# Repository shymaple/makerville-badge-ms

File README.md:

- `mkdir badge-workspace`
- `cd badge-workspace`
- `west init -m git@github.com:makerville/makerville-badge.git --mr master`
- `west update`
- `west blobs fetch hal_espressif`
- `cd makerville-badge`
- `make`
- `make flash monitor`

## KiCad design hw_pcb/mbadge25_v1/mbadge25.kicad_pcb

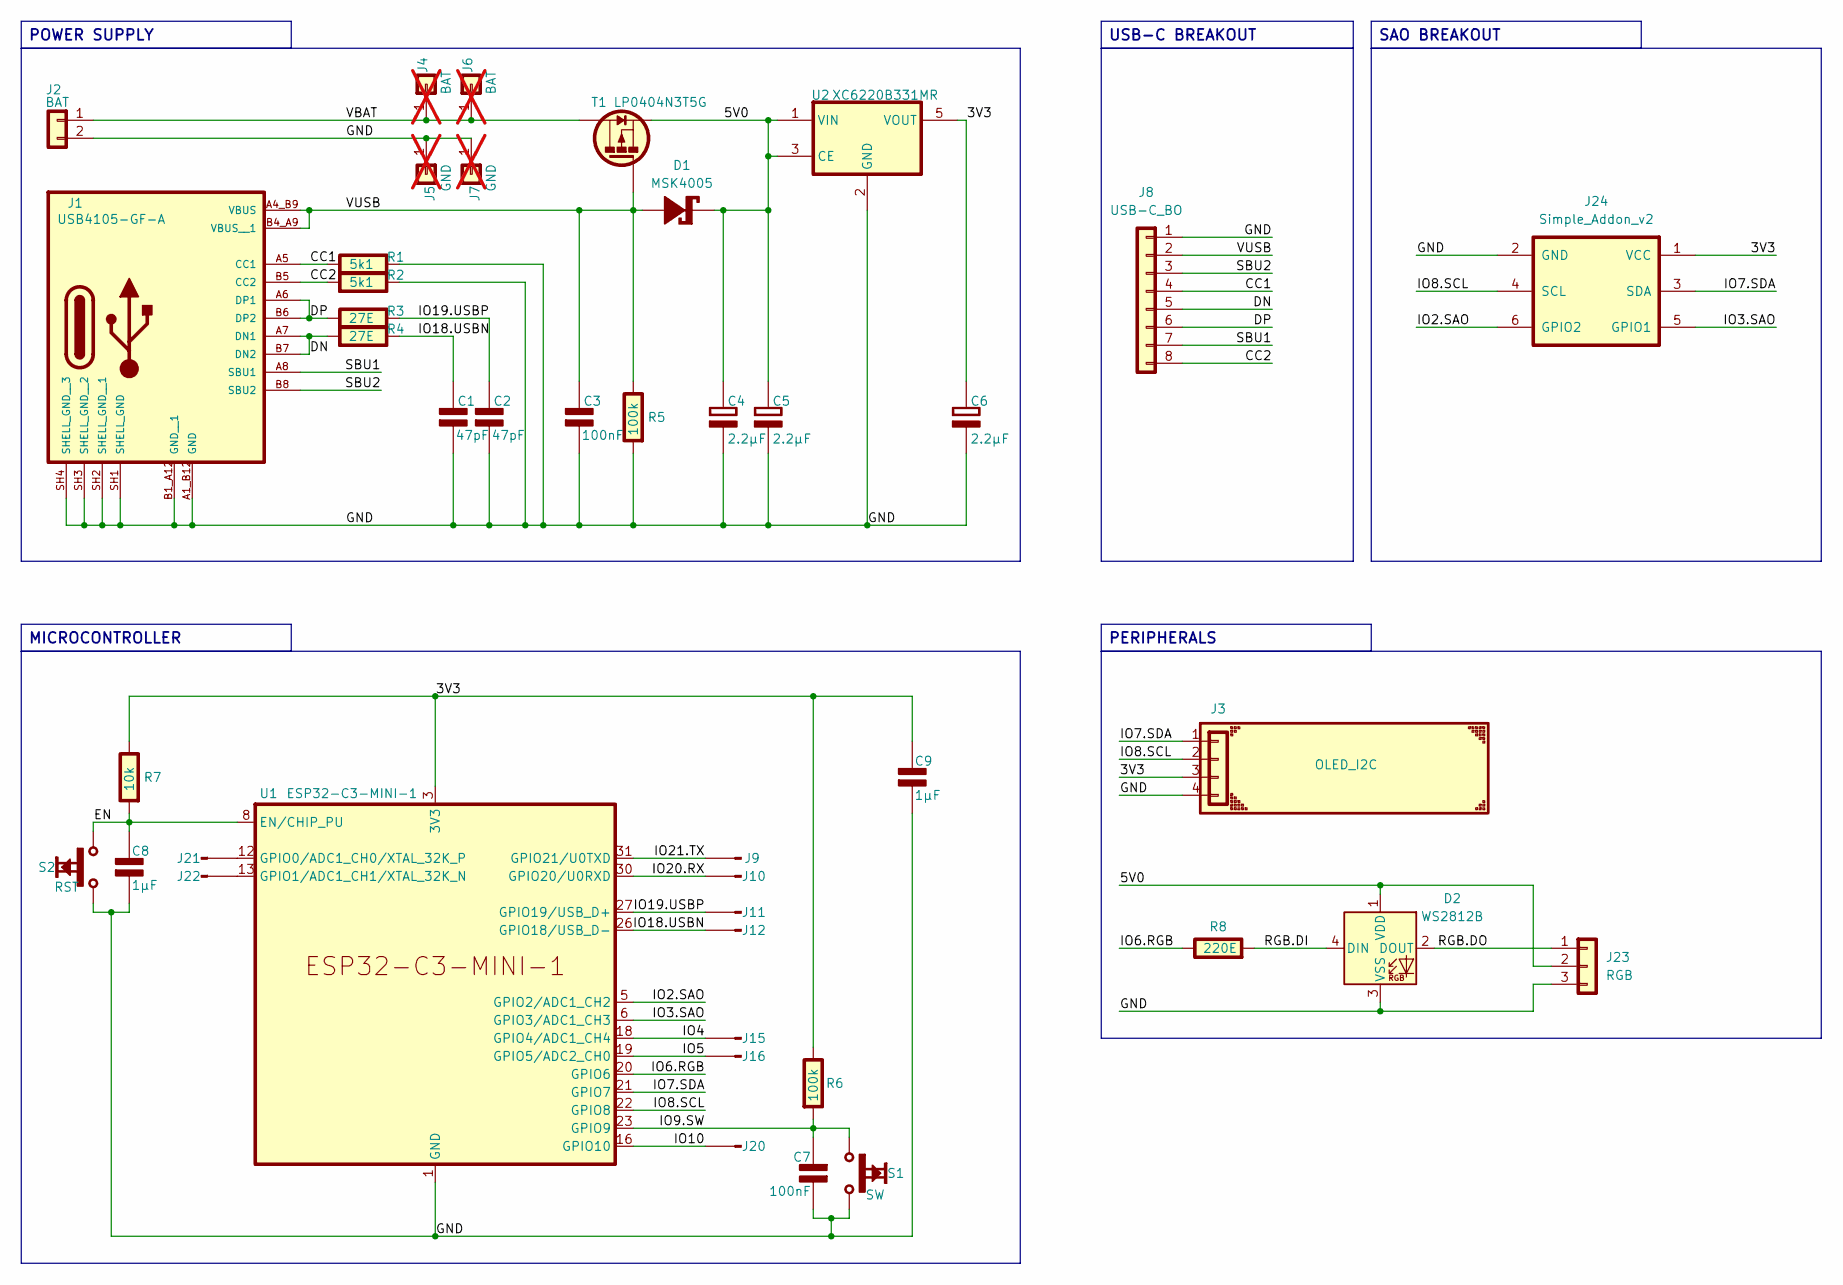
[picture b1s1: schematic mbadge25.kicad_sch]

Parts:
C1, C2: 47pF; C_1206_3216Metric_Pad1.33x1.80mm; Rating V
C3, C7: 100nF; C_1206_3216Metric_Pad1.33x1.80mm; Rating V
C4, C5, C6: 2.2µF; C_1206_3216Metric_Pad1.33x1.80mm; Rating V
C8, C9: 1µF; C_1206_3216Metric_Pad1.33x1.80mm; Rating V
D1: MSK4005; D_SOD-523; Rating V/A
D2: WS2812B; LED_WS2812B_PLCC4_5.0x5.0mm_P3.2mm
J1: USB4105-GF-A; GCT_USB4105-GF-A
J2: BAT; PinHeader_1x02_P2.54mm_Vertical
J3: OLED_I2C; OLED_128x32
J4: BAT; Pad_6.0mm_Drill3.0mm; not fitted
J5: GND; Pad_6.0mm_Drill3.0mm; not fitted
J6: BAT; Pad_1.2mm_Drill0.7mm; not fitted
J7: GND; Pad_1.2mm_Drill0.7mm; not fitted
J8: USB-C_BO; USB_C_BO
J9: Conn_IO21.TX; PinHeader_1x01_P1.27mm_Vertical
J10: Conn_IO20.RX; PinHeader_1x01_P1.27mm_Vertical
J11: Conn_IO19.USBP; PinHeader_1x01_P1.27mm_Vertical
J12: Conn_IO18.USBN; PinHeader_1x01_P1.27mm_Vertical
J15: Conn_IO4; PinHeader_1x01_P1.27mm_Vertical
J16: Conn_IO5; PinHeader_1x01_P1.27mm_Vertical
J20: Conn_IO10; PinHeader_1x01_P1.27mm_Vertical
J21: Conn_IO00; PinHeader_1x01_P1.27mm_Vertical
J22: Conn_IO01; PinHeader_1x01_P1.27mm_Vertical
J23: RGB; PinSocket_1x03_P1.27mm_Vertical
J24: Simple_Addon_v2; Simple_Addon_v2-BADGE-2x3
R1, R2: 5k1; R_1206_3216Metric_Pad1.30x1.75mm; Rating W
R3, R4: 27E; R_1206_3216Metric_Pad1.30x1.75mm; Rating W
R5, R6: 100k; R_1206_3216Metric_Pad1.30x1.75mm; Rating W
R7: 10k; R_1206_3216Metric_Pad1.30x1.75mm; Rating W
R8: 220E; R_1206_3216Metric_Pad1.30x1.75mm; Rating W
S1: SW; SW_SPST; Rating V/A
S2: RST; SW_SPST; Rating V/A
T1: LP0404N3T5G; SOT-23-3
U1: ESP32-C3-MINI-1
U2: XC6220B331MR; SOT-23-5_HandSoldering

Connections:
/3V3: C6.1 (+), C9.1 (+), J3.3, J24.1 (VCC), R6.2 (-), R7.2 (-), U1.3 (3V3), U2.5 (VOUT)
/5V0: C4.1 (+), C5.1 (+), D1.1 (K-), D2.1 (VDD), J23.2, T1.3 (S), U2.1 (VIN), U2.3 (CE)
/CC1: J1.A5 (CC1), J8.4, R1.1 (+)
/CC2: J1.B5 (CC2), J8.8, R2.1 (+)
/DN: J1.A7 (DN1), J1.B7 (DN2), J8.5, R4.1 (+)
/DP: J1.A6 (DP1), J1.B6 (DP2), J8.6, R3.1 (+)
/EN: C8.1 (+), R7.1 (+), S2.1, U1.8 (EN/CHIP_PU)
/GND: C1.2 (-), C2.2 (-), C3.2 (-), C4.2 (-), C5.2 (-), C6.2 (-), C7.2 (-), C8.2 (-), C9.2 (-), D2.3 (VSS), J1.A1_B12 (GND), J1.B1_A12 (GND__1), J1.SH1 (SHELL_GND), J1.SH2 (SHELL_GND__1), J1.SH3 (SHELL_GND__2), J1.SH4 (SHELL_GND__3), J2.2, J3.4, J5.1, J7.1, J8.1, J23.3, J24.2 (GND), R1.2 (-), R2.2 (-), R5.1 (+), S1.2, S2.2, U1.1 (GND), U1.2 (GND), U1.11 (GND), U1.14 (GND), U1.36 (GND), U1.37 (GND), U1.38 (GND), U1.39 (GND), U1.40 (GND), U1.41 (GND), U1.42 (GND), U1.43 (GND), U1.44 (GND), U1.45 (GND), U1.46 (GND), U1.47 (GND), U1.48 (GND), U1.49 (GND), U1.50 (GND), U1.51 (GND), U1.52 (GND), U1.53 (GND), U2.2 (GND)
/IO2.SAO: J24.6 (GPIO2), U1.5 (GPIO2/ADC1_CH2)
/IO3.SAO: J24.5 (GPIO1), U1.6 (GPIO3/ADC1_CH3)
/IO4: J15.1, U1.18 (GPIO4/ADC1_CH4)
/IO5: J16.1, U1.19 (GPIO5/ADC2_CH0)
/IO6.RGB: R8.2 (-), U1.20 (GPIO6)
/IO7.SDA: J3.1, J24.3 (SDA), U1.21 (GPIO7)
/IO8.SCL: J3.2, J24.4 (SCL), U1.22 (GPIO8)
/IO9.SW: C7.1 (+), R6.1 (+), S1.1, U1.23 (GPIO9)
/IO10: J20.1, U1.16 (GPIO10)
/IO18.USBN: C1.1 (+), J12.1, R4.2 (-), U1.26 (GPIO18/USB_D-)
/IO19.USBP: C2.1 (+), J11.1, R3.2 (-), U1.27 (GPIO19/USB_D+)
/IO20.RX: J10.1, U1.30 (GPIO20/U0RXD)
/IO21.TX: J9.1, U1.31 (GPIO21/U0TXD)
/RGB.DI: D2.4 (DIN), R8.1 (+)
/RGB.DO: D2.2 (DOUT), J23.1
/SBU1: J1.A8 (SBU1), J8.7
/SBU2: J1.B8 (SBU2), J8.3
/VBAT: J2.1, J4.1, J6.1, T1.1 (D)
/VUSB: C3.1 (+), D1.2 (A+), J1.A4_B9 (VBUS), J1.B4_A9 (VBUS__1), J8.2, R5.2 (-), T1.2 (G)
unnamed: J21.1, U1.12 (GPIO0/ADC1_CH0/XTAL_32K_P)
unnamed: J22.1, U1.13 (GPIO1/ADC1_CH1/XTAL_32K_N)

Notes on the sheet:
MICROCONTROLLER
POWER SUPPLY
USB-C BREAKOUT
SAO BREAKOUT
PERIPHERALS

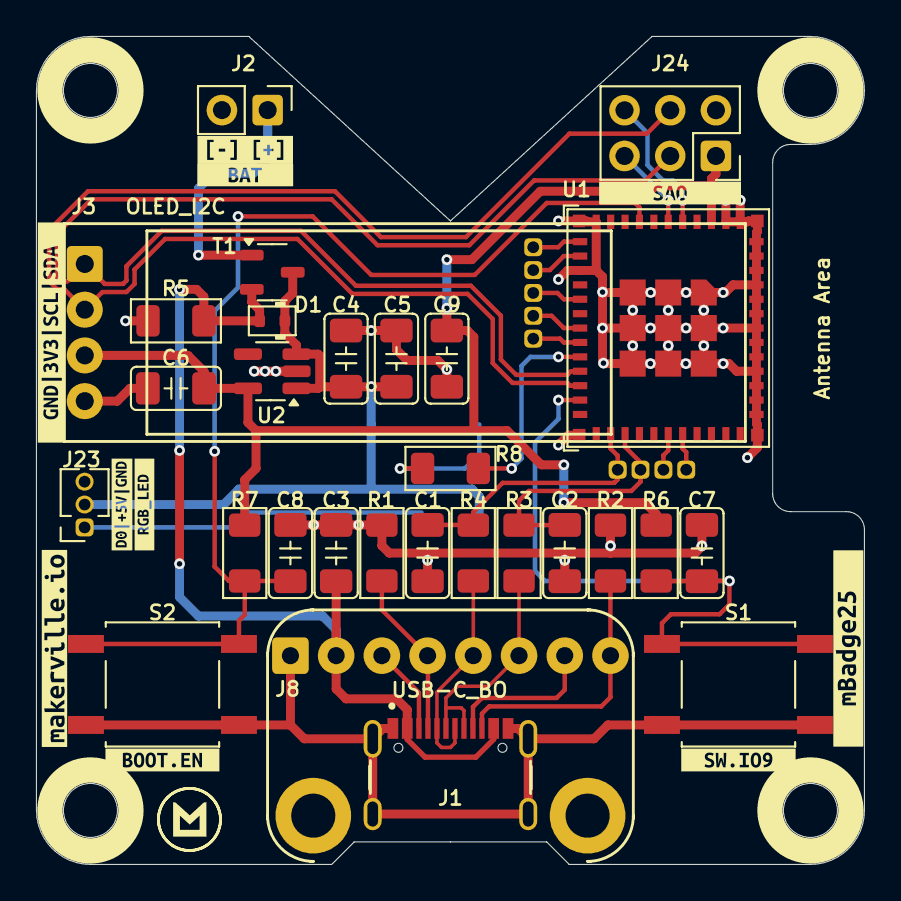
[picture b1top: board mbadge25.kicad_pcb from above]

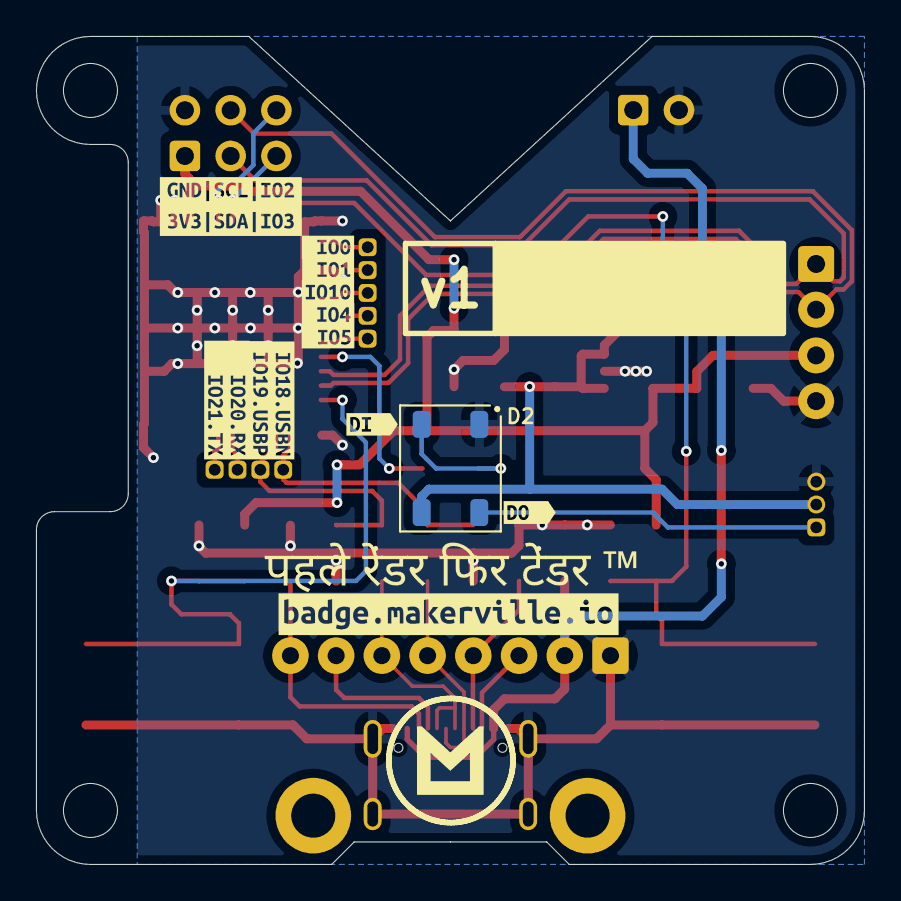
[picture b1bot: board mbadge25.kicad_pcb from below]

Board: 2 copper layers, 46.0 x 46.0 mm, 63 parts (15 on the bottom side), 29 nets.

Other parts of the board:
kibuzzard-67DC6E7C: G***; kibuzzard-67DC6E7C
kibuzzard-67DC6E31: G***; kibuzzard-67DC6E31
kibuzzard-67DC7C6A: G***; kibuzzard-67DC7C6A
kibuzzard-67DC7C9D: G***; kibuzzard-67DC7C9D
kibuzzard-67DC74C1: G***; kibuzzard-67DC74C1
kibuzzard-67DC7196: G***; kibuzzard-67DC7196
kibuzzard-67DC7478: G***; kibuzzard-67DC7478
kibuzzard-67DC7585: G***; kibuzzard-67DC7585
kibuzzard-67DDA9CA: G***; kibuzzard-67DDA9CA
kibuzzard-67DDA805: G***; kibuzzard-67DDA805
kibuzzard-67DDAA0B: G***; kibuzzard-67DDAA0B
kibuzzard-67DDAEB0: G***; kibuzzard-67DDAEB0
kibuzzard-67DDB00D: G***; kibuzzard-67DDB00D
kibuzzard-67DDB002: G***; kibuzzard-67DDB002
kibuzzard-67DDB04A: G***; kibuzzard-67DDB04A
kibuzzard-67DDB008: G***; kibuzzard-67DDB008
kibuzzard-67DDB012: G***; kibuzzard-67DDB012
kibuzzard-67DDB018: G***; kibuzzard-67DDB018
kibuzzard-67DDB039: G***; kibuzzard-67DDB039
kibuzzard-67DDB040: G***; kibuzzard-67DDB040
kibuzzard-67DDB045: G***; kibuzzard-67DDB045
kibuzzard-67E1BB32: G***; kibuzzard-67E1BB32
kibuzzard-67E02D12: G***; kibuzzard-67E02D12
kibuzzard-67E616D7: G***; kibuzzard-67E616D7

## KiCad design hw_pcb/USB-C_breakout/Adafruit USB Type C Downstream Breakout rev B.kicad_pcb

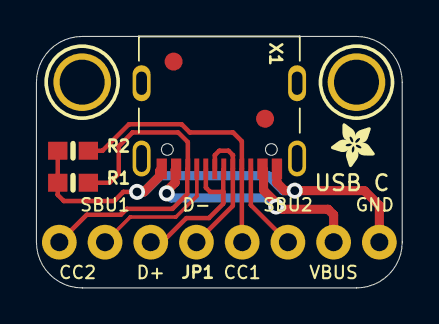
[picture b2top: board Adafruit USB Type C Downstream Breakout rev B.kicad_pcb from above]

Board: 2 copper layers, 20.3 x 14.0 mm, 10 parts (1 on the bottom side), 8 nets.

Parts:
FID1, FID2: FIDUCIAL_1MM
JP1: 1X08_ROUND_76
R1, R2: 5.1K; 0603-NO
U$1, U$2: MOUNTINGHOLE2.5; MOUNTINGHOLE_2.5_PLATED
U$3: ADAFRUIT_2.5MM
U$8: PCBFEAT-REV-040
X1: USB_C_CUSB31-CFM2AX-01-X

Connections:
CC1: JP1.4, R2.2, X1.A5
CC2: JP1.8, R1.2, X1.B5
D+: JP1.6, X1.A6, X1.B6
D-: JP1.5, X1.A7, X1.B7
GND: JP1.1, R1.1, R2.1, X1.A1B12, X1.B1A12
SBU1: JP1.7, X1.A8
SBU2: JP1.3, X1.B8
VBUS: JP1.2, X1.A4B9, X1.B4A9

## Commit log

2025-02-22 Init commit
2025-02-22 Add west.yml
2025-02-22 Minimal c3 build
2025-02-22 Use c3 devkitm
2025-02-23 Display simple text
2025-02-23 Remove kerning
2025-02-26 Add button code (commented as buggy)
    Seeing i2c crashes when button enabled - not sure why yet
2025-02-26 Use pin 7 for i2c - pin 9 used for onboard button
2025-02-27 Cycle through strings on button
2025-03-04 Missing flag in readme instructions
2025-03-05 schematic v1 WIP
2025-03-09 v1 draft PCB layout
2025-03-17 v2 draft PCB layout
2025-03-18 draft PCB layout WIP
2025-03-20 changed PCB dims, rearranged components
2025-03-21 PCB routing done, labels added
2025-03-23 simple sandwich enclosure design
2025-03-26 PCB updates
2025-03-28 Fix typo on silksceen
2025-03-30 iBoM and Render updates
2025-04-06 Create LICENSE
2025-05-16 Use usb serial for console, swap i2c pins based on schem
2025-05-17 Rename build file, check val before calling button callback
2025-05-17 mBadge_v2 updates : * Added v2 folder for hw_pcb * Added pull up for IO2 * Added pull up for IO8 (I2C) * Added pull up for IO7 (I2C) * Changed R6 from 100k to 10k * Legend, Replaced v1 with v2 * Lege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
2025-05-19 Add scrolling text
2025-05-21 Add enclosure
2025-05-22 Add buttons
2025-05-22 Add single STL
2025-05-22 Accept button input during scroll
2025-05-22 Get rid of flicker, increase scroll speed
2025-05-22 Remove unused variables
2025-05-25 Add state machine skeleton
2025-05-25 Add events and message queue to smf
2025-05-26 Show text on idle entry
2025-05-26 Change prompt shell
2025-05-26 Move to input subsys, have short and long button press events
2025-05-30 Add BLE read/write for text
2025-06-04 Fix warnings
2025-06-04 Add non deprecated flag
2025-06-04 Try restarting the advertising after a disconnect
    Fails with error -12 - need to dig more
2025-07-04 - Replaced D1. Previous MPN: MSK4005 (SOD-523) New MPN: B0520LW-7-F (SOD-123). - Replaced U2. Previous MPN : XC6220B331MR New MPN: AP7366-33W5-7. - Updated Mfr. Part Number for all components. - Adde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
2025-07-18 Update instructions
2025-09-05 Update to 4.2 zephyr
2025-10-15 update overlay for added neopixel gpio
2025-10-15 Enable LED strip
2025-10-15 Add Neopixel LED support with shell command
2025-10-26 Use linter for dts/overlay in make target
2025-10-30 Move led init to badge init, accept values between 0 and 255
2025-10-31 Add github workflow to push and deploy
2025-10-31 Fetch espressif blobs, use risc-v toolchain
2025-10-31 Make push bin name agnostic
2025-10-31 Dont archive artifacts on gh
2025-10-31 Dont use project name in workflow yaml
2025-10-31 Add GitHub Actions workflow for Zephyr build and deployment
2025-10-31 updated the code for the key
2025-10-31 Fix secret names for Embedhub deployment
    Corrected secret names for organization and project in Embedhub deployment.
2025-10-31 Updated as per Makerville badge
2025-10-31 Changed org name and project name
2025-10-31 Corrected org name and org project
2025-10-31 Updated APi key name
2025-10-31 Again used Makerville yml
2025-10-31 Update badge name in BLE service and display
    Makerville Badge MS
